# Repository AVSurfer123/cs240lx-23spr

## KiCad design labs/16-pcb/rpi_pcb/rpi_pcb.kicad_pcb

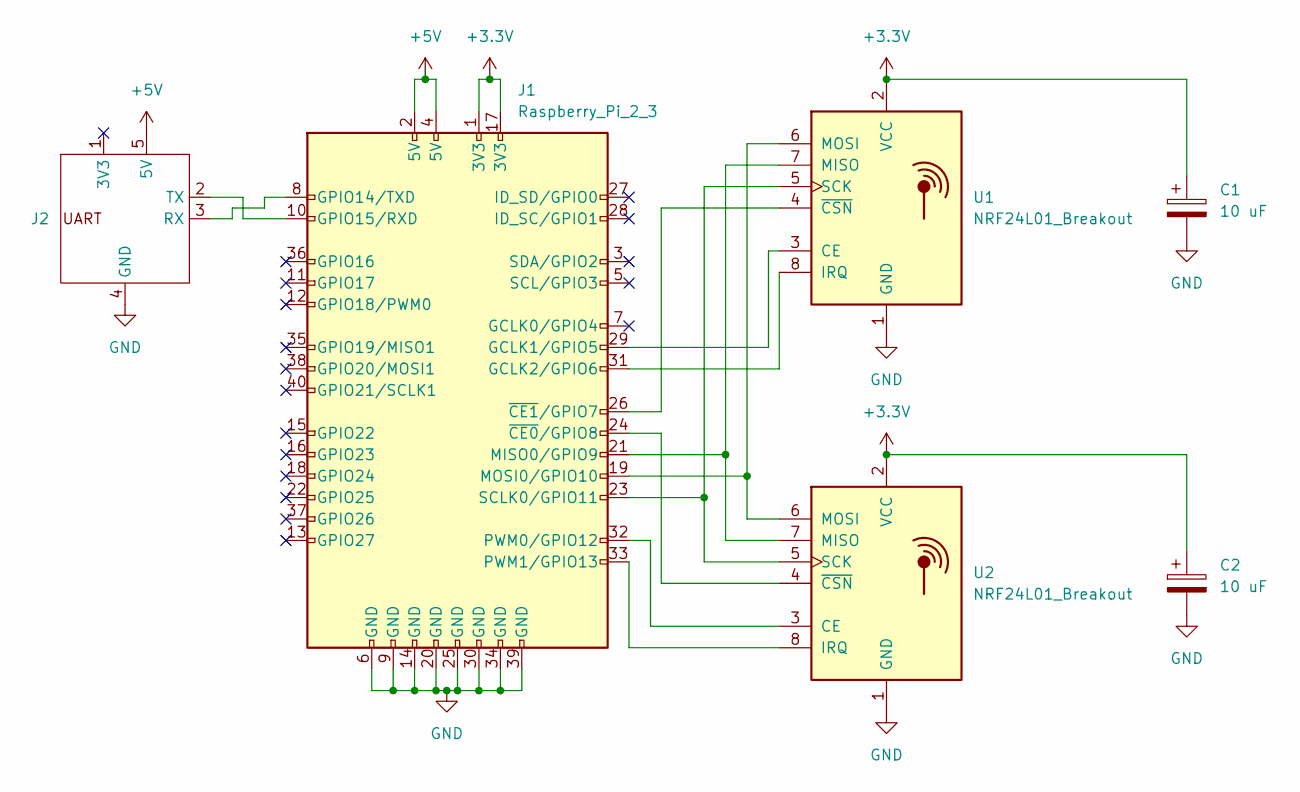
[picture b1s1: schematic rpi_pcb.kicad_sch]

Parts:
C1, C2: 10 uF; CP_Elec_4x5.4
J1: Raspberry_Pi_2_3; PinSocket_2x20_P2.54mm_Vertical
J2: PinSocket_1x05_P2.54mm_Horizontal
U1, U2: NRF24L01_Breakout; nRF24L01_Breakout

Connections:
+3.3V: C1.1, C2.1, J1.1 (3V3), J1.17 (3V3), U1.2 (VCC), U2.2 (VCC)
+5V: J1.2 (5V), J1.4 (5V), J2.5 (5V)
GND: C1.2, C2.2, J1.6 (GND), J1.9 (GND), J1.14 (GND), J1.20 (GND), J1.25 (GND), J1.30 (GND), J1.34 (GND), J1.39 (GND), J2.4 (GND), U1.1 (GND), U2.1 (GND)
unnamed: J1.29 (GCLK1/GPIO5), U1.3 (CE)
unnamed: J1.31 (GCLK2/GPIO6), U1.8 (IRQ)
unnamed: J1.8 (GPIO14/TXD), J2.3 (RX)
unnamed: J1.10 (GPIO15/RXD), J2.2 (TX)
unnamed: J1.21 (MISO0/GPIO9), U1.7 (MISO), U2.7 (MISO)
unnamed: J1.19 (MOSI0/GPIO10), U1.6 (MOSI), U2.6 (MOSI)
unnamed: J1.32 (PWM0/GPIO12), U2.3 (CE)
unnamed: J1.33 (PWM1/GPIO13), U2.8 (IRQ)
unnamed: J1.23 (SCLK0/GPIO11), U1.5 (SCK), U2.5 (SCK)
unnamed: J1.24 (~CE0/GPIO8), U2.4 (~CSN)
unnamed: J1.26 (~CE1/GPIO7), U1.4 (~CSN)

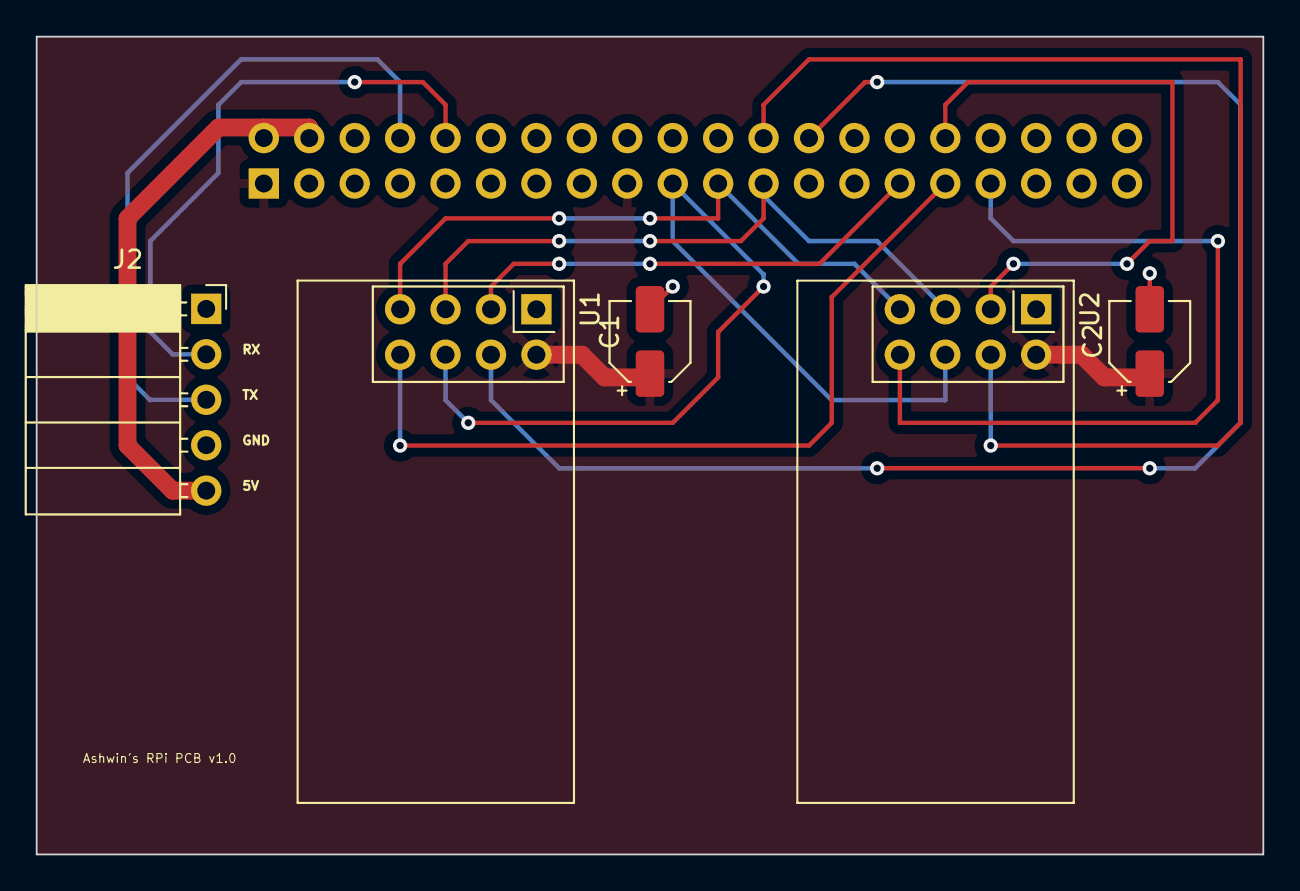
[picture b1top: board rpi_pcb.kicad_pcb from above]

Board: 2 copper layers, 68.6 x 45.7 mm, 6 parts (1 on the bottom side), 14 nets.

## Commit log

2023-06-02 Finished lab 1
2023-06-02 Finished lab 2
2023-06-02 Finished lab 9
2023-06-02 WIP lab 11
2023-06-02 Madgewick filter extension
2023-06-02 Finished lab 8
2023-06-02 Finished lab 4,5
2023-06-02 Finished lab 6 (rest of lab 5)
2023-06-02 Finished lab 13
2023-06-02 Finished lab 3
2023-06-02 Finished lab 7
2023-06-02 WIP lab 10
2023-06-02 Finished lab 12
2023-06-02 Updating i2c speed for mpu, adding interrupt code
2023-06-02 Added support for both imus in mpu driver
2023-06-02 Adding fp to led code
2023-06-02 Working gimbal
2023-06-02 Finished lab 15
2023-06-02 Finished lab 16
2023-06-02 Fixed lab 11 i2s driver, added parthiv's fft code
2023-06-02 Finished lab 11
2023-06-07 Finished lab 17
2023-06-13 Checked off labs 7 and 10
2023-06-13 Split gimbal code into separate file
2023-06-13 Finished lab 14, playing music
2023-06-13 Removing pcb backup files
